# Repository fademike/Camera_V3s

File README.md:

# Camera_V3s
Webcam based on allwinner V3s and ESP8089

Simple 2 side board with Allwinner V3s, ov2640 and esp8089! 
(I didn't check the sound)

# How it works
Change wifi settings in file CONFIG_FILE <br>
Find ip in network by name. For example fing app: 
<br>
Watch the video on the MXPlayer(rtsp://192.168.10.22:8554/test), ffmpeg (ffplay -i rtsp://192.168.10.22:8554/test).. <br>
Watch the video on the Gstreamer: gst-launch-1.0 rtspsrc location="rtsp://192.168.10.22:8554/test" latency=0 ! rtph264depay ! decodebin ! videoconvert ! ximagesink <br>

# for QGroundControl:
TX: gst-launch-1.0 -v v4l2src device=/dev/video0 ! "video/x-raw,format=UYVY,width=800,height=600,framerate=10/1" ! videoconvert ! cedar_h264enc bitrate=2000 qp=15 keyint=10 ! rtph264pay pt=96 ! udpsink host=192.168.10.14 port=5600 <br>
RX on QGC or gstreamer: gst-launch-1.0 -v udpsrc port=5600 ! "application/x-rtp, media=(string)video, clock-rate=(int)90000, encoding-name=(string)H264, payload=(int)96" ! rtph264depay ! h264parse ! avdec_h264 ! videoconvert ! autovideosink <br>

v1.4 changed scheme and pcb. didn't check <br>
v1.2 in the previous commit. it works but there are errors errataSheet.txt in kicad

top             |  bottom
:-------------------------:|:-------------------------:
  |  

# How to build

git clone https://github.com/fademike/buildroot_v3s.git <br>
tar xf ~/Downloads/buildroot-2023.08.tar.xz <br>
cd buildroot-2023.08 <br>
ln -s ~/Downloads/buildroot/dl ./dl  # if you want <br>
make BR2_EXTERNAL=../buildroot_v3s licheepi_zero_defconfig (in dts you can change size of NOR flash) <br>
make <br>
make esp-rebuild && make <br>

# How to install

insert sd card.. <br>
./make_sd.sh <br>
run board camera_v3s from flash <br>
mount /dev/mmcblk0p1 /mnt <br>
flashcp /mnt/uboot_spi.bin /dev/mtd0 -v <br>
flashcp /mnt/zImage /dev/mtd1 -v <br>
flashcp /mnt/uboot_spi.bin /dev/mtd2 -v <br>
flashcp /mnt/rootfs.squashfs /dev/mtd3 -v <br>
flash_erase /dev/mtd4 0 1000.. <br>
add to mtd4 CONFIG_FILE to wifi settings, and init/deinit script of system <br>
init.sh script for example: <br>
test-launch  --gst-debug=3 '( v4l2src device=/dev/video0 ! video/x-raw,format=UYVY,width=800,height=600,framerate=10/1 ! videoconvert ! cedar_h264enc bitrate=2000 qp=15 keyint=10 ! rtph264pay name=pay0 pt=96 )' &

# note

The wi-fi is crashes after 30-50min. It was discussed on the forum (https://whycan.com/t_4326.html). I would like to change it to XR819, 88W8801 or others. 
You can connect usb wifi adapter (such as MT7601U) or solder a USB wifi module on bottom side.
I didn't notice any problems with the usb wifi adapter.

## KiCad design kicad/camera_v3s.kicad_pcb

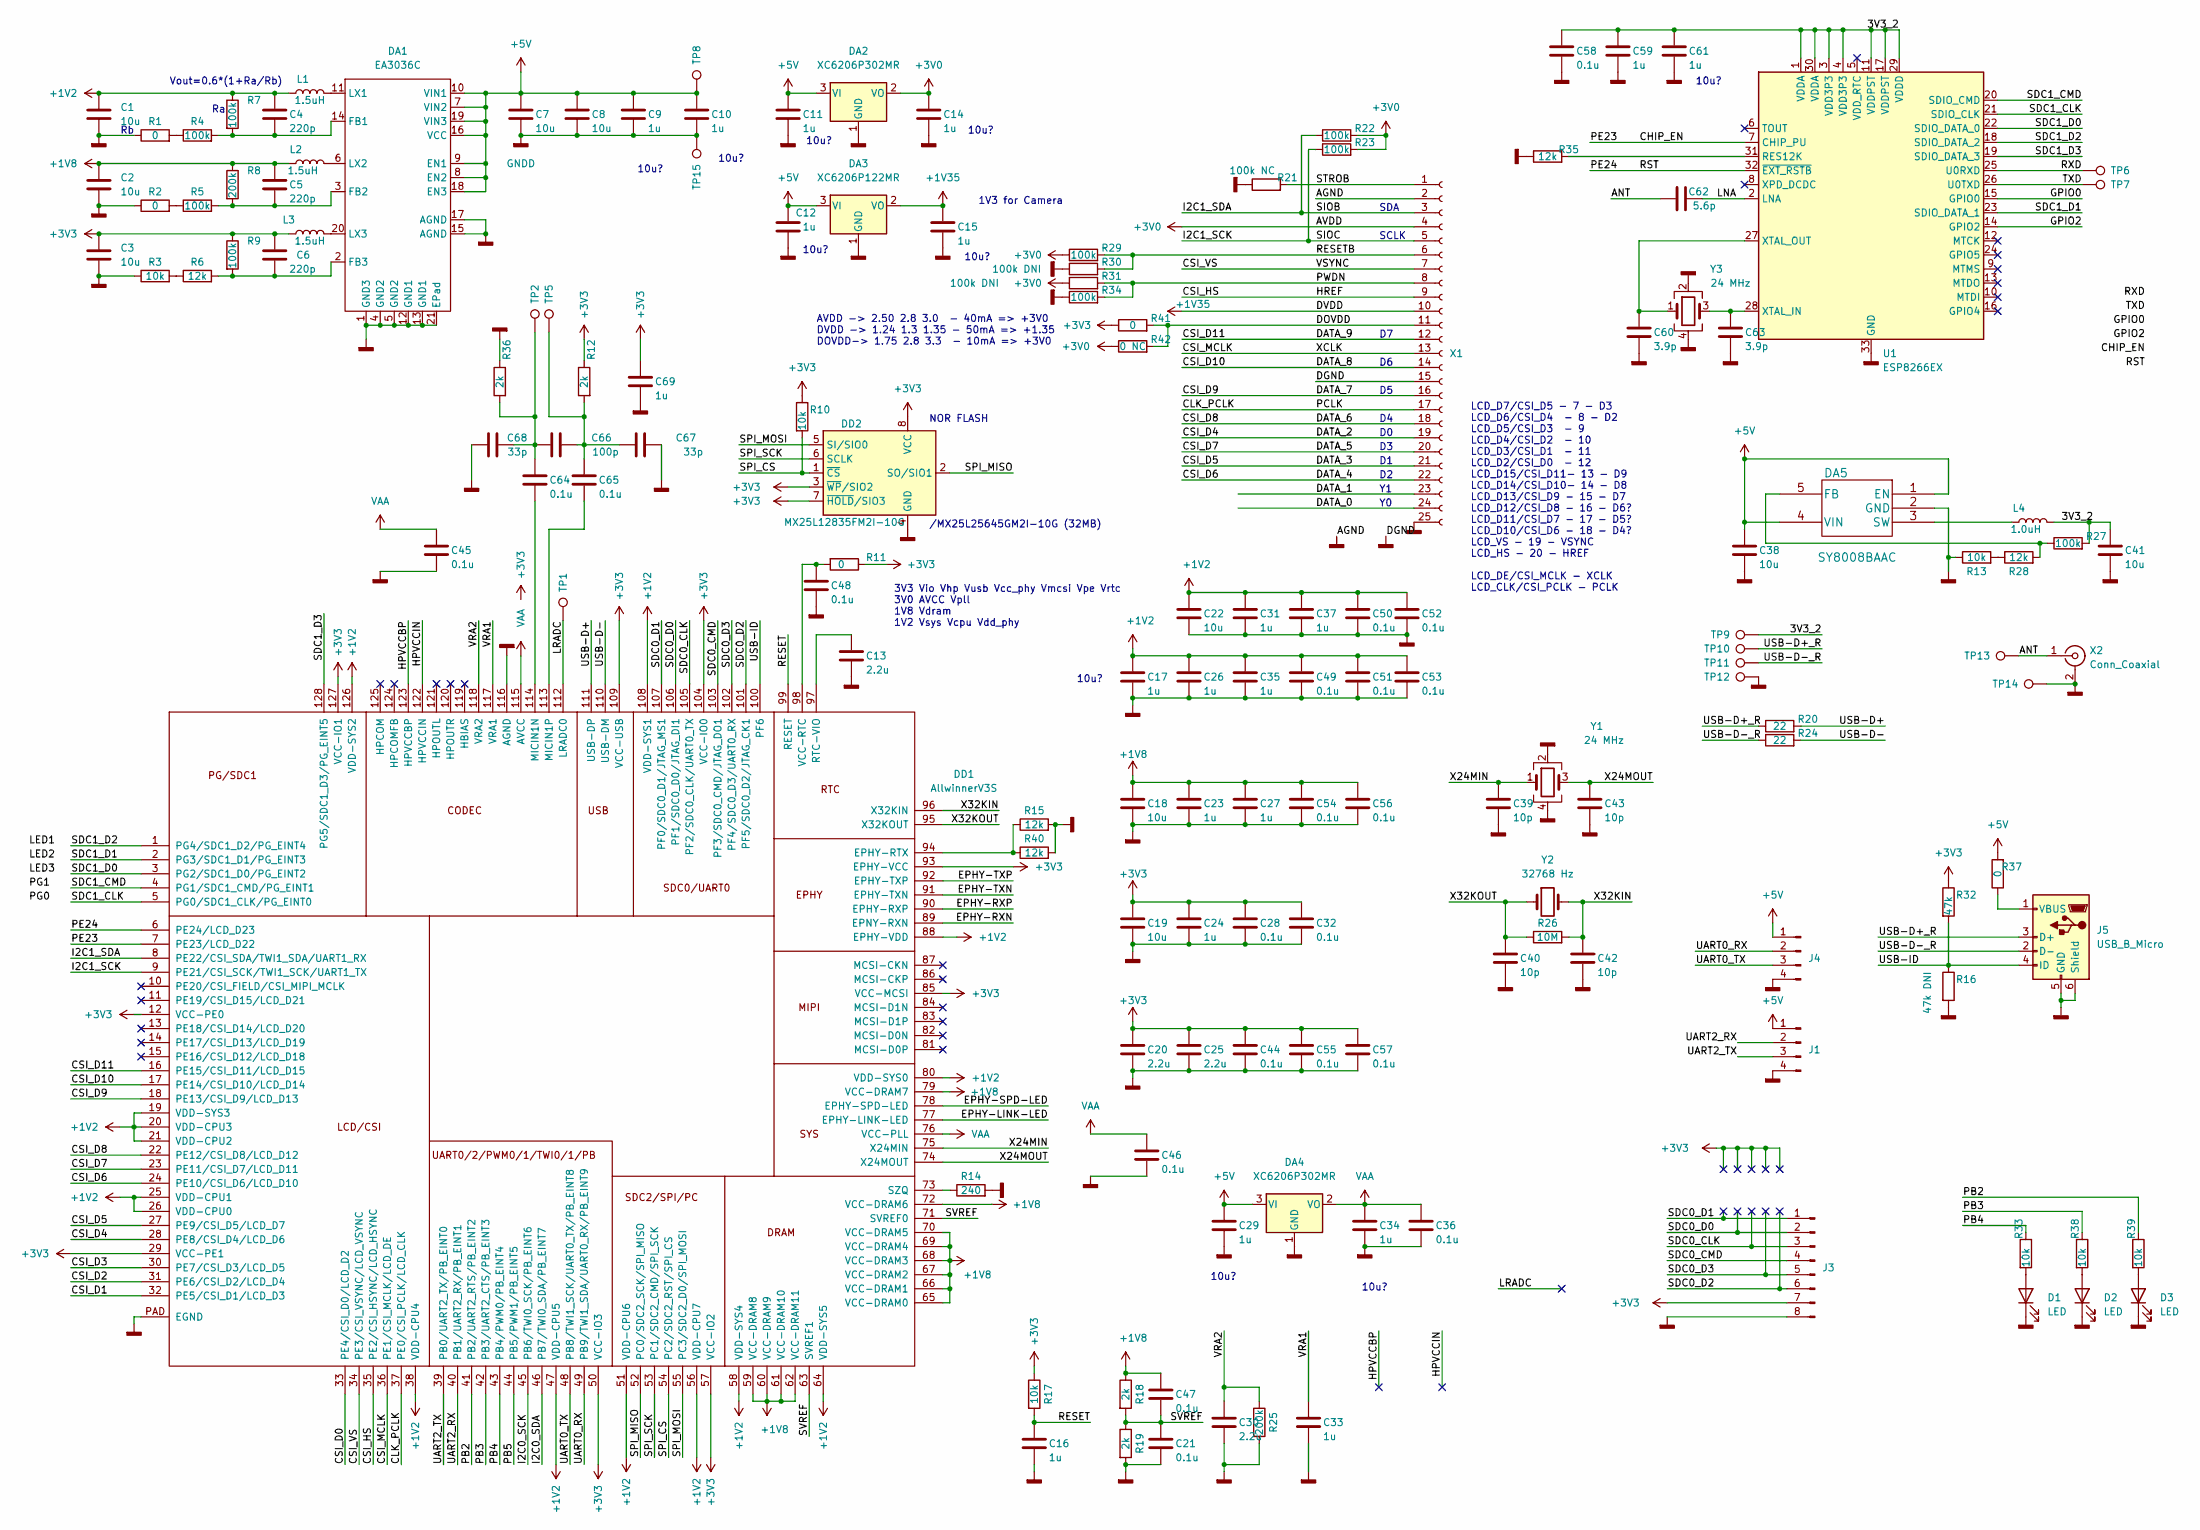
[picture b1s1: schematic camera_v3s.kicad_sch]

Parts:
C1, C2, C3, C7, C8, C18, C19, C22, C38, C41: 10u; C_0603_1608Metric; Voltage 6.3V
C4, C5, C6: 220p; C_0402_1005Metric; Voltage 6.3V
C9, C10, C11, C12, C14, C15, C16, C17, C23, C24, C26, C27, C29, C31, C33, C34, C35, C37, C59, C61, C69: 1u; C_0402_1005Metric; Voltage 6.3V
C13, C20, C25, C30: 2.2u; C_0402_1005Metric; Voltage 6.3V
C21, C28, C32, C36, C44, C45, C46, C47, C48, C49, C50, C51, C52, C53, C54, C55, C56, C57, C58, C64, C65: 0.1u; C_0402_1005Metric; Voltage 6.3V
C39, C40, C42, C43: 10p; C_0402_1005Metric; Voltage 6.3V
C60, C63: 3.9p; C_0402_1005Metric; Voltage 6.3V
C62: 5.6p; C_0402_1005Metric; Voltage 6.3V
C66: 100p; C_0402_1005Metric; Voltage 6.3V
C67, C68: 33p; C_0402_1005Metric; Voltage 6.3V
D1, D2, D3: LED; LED_0603_1608Metric
DA1: EA3036C; QFN-20-1EP_3x3mm_P0.4mm_EP1.65x1.65mm
DA2, DA4: XC6206P302MR; SOT-23
DA3: XC6206P122MR; SOT-23
DA5: SY8008BAAC; SOT-23-5
DD1: AllwinnerV3S; LQFP-128_14x14mm_P0.4mm
DD2: MX25L12835FM2I-10G; SOP-8_5.28x5.23mm_P1.27mm
J1, J4: Conn_01x04_Male; Molex_PicoBlade_53047-0410_1x04_P1.25mm_Vertical
J3: Conn_01x08_Male; Molex_PicoBlade_53047-0810_1x08_P1.25mm_Vertical
J5: USB_B_Micro; USB_Micro-B_Molex_47346-0001
L1, L2, L3: 1.5uH; L_1210_3225Metric
L4: 1.0uH; L_1210_3225Metric
R1, R2, R11, R41: 0; R_0402_1005Metric
R3, R10, R13, R17, R33, R38, R39: 10k; R_0402_1005Metric
R4, R5, R7, R9, R22, R23, R27, R29, R34: 100k; R_0402_1005Metric
R6, R15, R28, R35, R40: 12k; R_0402_1005Metric
R8, R25: 200k; R_0402_1005Metric
R12, R18, R19, R36: 2k; R_0402_1005Metric
R14: 240; R_0402_1005Metric
R16: 47k DNI; R_0402_1005Metric
R20, R24: 22; R_0402_1005Metric
R21: 100k NC; R_0402_1005Metric
R26: 10M; R_0402_1005Metric
R30, R31: 100k DNI; R_0402_1005Metric
R32: 47k; R_0402_1005Metric
R37: 0; R_0603_1608Metric
R42: 0 NC; R_0402_1005Metric
TP1, TP2, TP5, TP6, TP7, TP8, TP9, TP10, TP11, TP12, TP13, TP14, TP15: TestPoint; TestPoint_Pad_D1.0mm
U1: ESP8266EX; QFN-32-1EP_5x5mm_P0.5mm_EP3.45x3.45mm
X1: Conn_01x25_Female; CONN_FPC_24_0.5
X2: Conn_Coaxial; U.FL_Molex_MCRF_73412-0110_Vertical
Y1, Y3: 24 MHz; Crystal_SMD_3225-4Pin_3.2x2.5mm
Y2: 32768 Hz; Crystal_SMD_3215-2Pin_3.2x1.5mm

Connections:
+1V2: C1.1, C4.1, C17.1, C22.1, C26.1, C31.1, C35.1, C37.1, C49.1, C50.1, C51.1, C52.1, C53.1, DD1.19 (VDD-SYS3), DD1.20 (VDD-CPU3), DD1.21 (VDD-CPU2), DD1.25 (VDD-CPU1), DD1.26 (VDD-CPU0), DD1.38 (VDD-CPU4), DD1.47 (VDD-CPU5), DD1.51 (VDD-CPU6), DD1.56 (VDD-CPU7), DD1.58 (VDD-SYS4), DD1.64 (VDD-SYS5), DD1.80 (VDD-SYS0), DD1.88 (EPHY-VDD), DD1.108 (VDD-SYS1), DD1.126 (VDD-SYS2), L1.1, R7.1
+1V8: C2.1, C5.1, C18.1, C23.1, C27.1, C47.1, C54.1, C56.1, DD1.59 (VCC-DRAM8), DD1.60 (VCC-DRAM9), DD1.61 (VCC-DRAM10), DD1.62 (VCC-DRAM11), DD1.65 (VCC-DRAM0), DD1.66 (VCC-DRAM1), DD1.67 (VCC-DRAM2), DD1.68 (VCC-DRAM3), DD1.69 (VCC-DRAM4), DD1.70 (VCC-DRAM5), DD1.72 (VCC-DRAM6), DD1.79 (VCC-DRAM7), L2.1, R8.1, R18.1
+1V35: C15.1, DA3.2 (VO), X1.10
+3V0: C14.1, DA2.2 (VO), R22.2, R23.2, R29.1, R31.1, R42.1, X1.4
+3V3: C3.1, C6.1, C19.1, C20.1, C24.1, C25.1, C28.1, C32.1, C44.1, C55.1, C57.1, C69.1, DD1.12 (VCC-PE0), DD1.29 (VCC-PE1), DD1.50 (VCC-IO3), DD1.57 (VCC-IO2), DD1.85 (VCC-MCSI), DD1.93 (EPHY-VCC), DD1.104 (VCC-IO0), DD1.109 (VCC-USB), DD1.127 (VCC-IO1), DD2.3 (~WP/SIO2), DD2.7 (~HOLD/SIO3), DD2.8 (VCC), J3.7, L3.1, R9.1, R10.1, R11.1, R12.1, R17.1, R32.1, R41.1
+5V: C7.1, C8.1, C9.1, C10.1, C11.1, C12.1, C29.1, C38.1, DA1.7 (VIN2), DA1.8 (EN2), DA1.9 (EN1), DA1.10 (VIN1), DA1.16 (VCC), DA1.18 (EN3), DA1.19 (VIN3), DA2.3 (VI), DA3.3 (VI), DA4.3 (VI), DA5.1 (EN), DA5.4 (VIN), J1.1, J4.1, R37.2, TP8.1
/3V3_2: C41.1, C58.1, C59.1, C61.1, L4.2, R27.2, TP9.1, U1.1 (VDDA), U1.3 (VDD3P3), U1.4 (VDD3P3), U1.11 (VDDPST), U1.17 (VDDPST), U1.29 (VDDD), U1.30 (VDDA)
/ANT: C62.1, TP13.1, X2.1 (In)
/CHIP_EN: DD1.7 (PE23/LCD_D22), U1.7 (CHIP_PU)
/CLK_PCLK: DD1.37 (PE0/CSI_PCLK/LCD_CLK), X1.17
/CSI_D0: DD1.33 (PE4/CSI_D0/LCD_D2)
/CSI_D1: DD1.32 (PE5/CSI_D1/LCD_D3)
/CSI_D2: DD1.31 (PE6/CSI_D2/LCD_D4)
/CSI_D3: DD1.30 (PE7/CSI_D3/LCD_D5)
/CSI_D4: DD1.28 (PE8/CSI_D4/LCD_D6), X1.19
/CSI_D5: DD1.27 (PE9/CSI_D5/LCD_D7), X1.21
/CSI_D6: DD1.24 (PE10/CSI_D6/LCD_D10), X1.22
/CSI_D7: DD1.23 (PE11/CSI_D7/LCD_D11), X1.20
/CSI_D8: DD1.22 (PE12/CSI_D8/LCD_D12), X1.18
/CSI_D9: DD1.18 (PE13/CSI_D9/LCD_D13), X1.16
/CSI_D10: DD1.17 (PE14/CSI_D10/LCD_D14), X1.14
/CSI_D11: DD1.16 (PE15/CSI_D11/LCD_D15), X1.12
/CSI_HS: DD1.35 (PE2/CSI_HSYNC/LCD_HSYNC), X1.9
/CSI_MCLK: DD1.36 (PE1/CSI_MCLK/LCD_DE), X1.13
/CSI_VS: DD1.34 (PE3/CSI_VSYNC/LCD_VSYNC), X1.7
/DATA_0: X1.24
/DATA_1: X1.23
/DOVDD: R41.2, R42.2, X1.11
/EPHY-LINK-LED: DD1.77 (EPHY-LINK-LED)
/EPHY-RXN: DD1.89 (EPNY-RXN)
/EPHY-RXP: DD1.90 (EPHY-RXP)
/EPHY-SPD-LED: DD1.78 (EPHY-SPD-LED)
/EPHY-TXN: DD1.91 (EPHY-TXN)
/EPHY-TXP: DD1.92 (EPHY-TXP)
/GPIO0: U1.15 (GPIO0)
/GPIO2: U1.14 (GPIO2)
/HPVCCBP: DD1.123 (HPVCCBP)
/HPVCCIN: DD1.122 (HPVCCIN)
/I2C0_SCK: DD1.45 (PB6/TWI0_SCK/PB_EINT6)
/I2C0_SDA: DD1.46 (PB7/TWI0_SDA/PB_EINT7)
/I2C1_SCK: DD1.9 (PE21/CSI_SCK/TWI1_SCK/UART1_TX), R23.1, X1.5
/I2C1_SDA: DD1.8 (PE22/CSI_SDA/TWI1_SDA/UART1_RX), R22.1, X1.3
/LNA: C62.2, U1.2 (LNA)
/LRADC: DD1.112 (LRADC0), TP1.1
/PB2: DD1.41 (PB2/UART2_RTS/PB_EINT2), R39.1
/PB3: DD1.42 (PB3/UART2_CTS/PB_EINT3), R38.1
/PB4: DD1.43 (PB4/PWM0/PB_EINT4), R33.1
/PB5: DD1.44 (PB5/PWM1/PB_EINT5)
/PE24: DD1.6 (PE24/LCD_D23), U1.32 (~EXT_RSTB)
/PWDN: R31.2, R34.2, X1.8
/RESET: C16.1, DD1.99 (RESET), R17.2
/RESETB: R29.2, R30.2, X1.6
/RXD: TP6.1, U1.25 (U0RXD)
/SDC0_CLK: DD1.105 (PF2/SDC0_CLK/UART0_TX), J3.3
/SDC0_CMD: DD1.103 (PF3/SDC0_CMD/JTAG_DO1), J3.4
/SDC0_D0: DD1.106 (PF1/SDC0_D0/JTAG_DI1), J3.2
/SDC0_D1: DD1.107 (PF0/SDC0_D1/JTAG_MS1), J3.1
/SDC0_D2: DD1.101 (PF5/SDC0_D2/JTAG_CK1), J3.6
/SDC0_D3: DD1.102 (PF4/SDC0_D3/UART0_RX), J3.5
/SDC1_CLK: DD1.5 (PG0/SDC1_CLK/PG_EINT0), U1.21 (SDIO_CLK)
/SDC1_CMD: DD1.4 (PG1/SDC1_CMD/PG_EINT1), U1.20 (SDIO_CMD)
/SDC1_D0: DD1.3 (PG2/SDC1_D0/PG_EINT2), U1.22 (SDIO_DATA_0)
/SDC1_D1: DD1.2 (PG3/SDC1_D1/PG_EINT3), U1.23 (SDIO_DATA_1)
/SDC1_D2: DD1.1 (PG4/SDC1_D2/PG_EINT4), U1.18 (SDIO_DATA_2)
/SDC1_D3: DD1.128 (PG5/SDC1_D3/PG_EINT5), U1.19 (SDIO_DATA_3)
/SPI_CS: DD1.54 (PC2/SDC2_RST/SPI_CS), DD2.1 (~CS), R10.2
/SPI_MISO: DD1.52 (PC0/SDC2_SCK/SPI_MISO), DD2.2 (SO/SIO1)
/SPI_MOSI: DD1.55 (PC3/SDC2_D0/SPI_MOSI), DD2.5 (SI/SIO0)
/SPI_SCK: DD1.53 (PC1/SDC2_CMD/SPI_SCK), DD2.6 (SCLK)
/STROB: R21.2, X1.1
/SVREF: C21.1, C47.2, DD1.63 (SVREF1), DD1.71 (SVREF0), R18.2, R19.1
/TXD: TP7.1, U1.26 (U0TXD)
/UART0_RX: DD1.49 (PB9/TWI1_SDA/UART0_RX/PB_EINT9), J4.2
/UART0_TX: DD1.48 (PB8/TWI1_SCK/UART0_TX/PB_EINT8), J4.3
/UART2_RX: DD1.40 (PB1/UART2_RX/PB_EINT1), J1.2
/UART2_TX: DD1.39 (PB0/UART2_TX/PB_EINT0), J1.3
/USB-D+: DD1.111 (USB-DP), R20.2
/USB-D+_R: J5.3 (D+), R20.1, TP10.1
/USB-D-: DD1.110 (USB-DM), R24.2
/USB-D-_R: J5.2 (D-), R24.1, TP11.1
/USB-ID: DD1.100 (PF6), J5.4 (ID), R16.1, R32.2
/VRA1: C33.1, DD1.117 (VRA1)
/VRA2: C30.1, DD1.118 (VRA2), R25.1
/X24MIN: C39.1, DD1.75 (X24MIN), Y1.1
/X24MOUT: C43.1, DD1.74 (X24MOUT), Y1.3
/X32KIN: C42.1, DD1.96 (X32KIN), R26.2, Y2.2
/X32KOUT: C40.1, DD1.95 (X32KOUT), R26.1, Y2.1
GNDD: C1.2, C2.2, C3.2, C7.2, C8.2, C9.2, C10.2, C11.2, C12.2, C13.2, C14.2, C15.2, C16.2, C17.2, C18.2, C19.2, C20.2, C21.2, C22.2, C23.2, C24.2, C25.2, C26.2, C27.2, C28.2, C29.2, C30.2, C31.2, C32.2, C33.2, C34.2, C35.2, C36.2, C37.2, C38.2, C39.2, C40.2, C41.2, C42.2, C43.2, C44.2, C45.2, C46.2, C48.2, C49.2, C50.2, C51.2, C52.2, C53.2, C54.2, C55.2, C56.2, C57.2, C58.2, C59.2, C60.2, C61.2, C63.2, C67.2, C68.1, C69.2, D1.1 (K), D2.1 (K), D3.1 (K), DA1.1 (GND3), DA1.4 (GND2), DA1.5 (GND2), DA1.12 (GND1), DA1.13 (GND1), DA1.15 (AGND), DA1.17 (AGND), DA1.21 (EPad), DA2.1 (GND), DA3.1 (GND), DA4.1 (GND), DA5.2 (GND), DD1.116 (AGND), DD1.PAD (EGND), DD2.4 (GND), J1.4, J3.8, J4.4, J5.5 (GND), J5.6 (Shield), R1.1, R2.1, R3.1, R13.1, R14.2, R15.2, R16.2, R19.2, R21.1, R25.2, R30.1, R34.1, R35.1, R36.1, R40.2, TP12.1, TP14.1, TP15.1, U1.33 (GND), X1.2, X1.15, X1.25, X2.2 (Ext), Y1.2, Y1.4, Y3.2, Y3.4
unnamed: C64.1, C66.1, C68.2, R36.2, TP2.1
unnamed: C65.1, C66.2, C67.1, R12.2, TP5.1
unnamed: D1.2 (A), R33.2
unnamed: D2.2 (A), R38.2
unnamed: D3.2 (A), R39.2
unnamed: C4.2, DA1.14 (FB1), R4.2, R7.2
unnamed: C5.2, DA1.3 (FB2), R5.2, R8.2
unnamed: C6.2, DA1.2 (FB3), R6.2, R9.2
unnamed: DA1.11 (LX1), L1.2
unnamed: DA1.6 (LX2), L2.2
unnamed: DA1.20 (LX3), L3.2
unnamed: DA5.5 (FB), R27.1, R28.2
unnamed: DA5.3 (SW), L4.1
unnamed: DD1.94 (EPHY-RTX), R15.1, R40.1
unnamed: C64.2, DD1.114 (MICIN1N)
unnamed: C65.2, DD1.113 (MICIN1P)
unnamed: C13.1, DD1.97 (RTC-VIO)
unnamed: DD1.73 (SZQ), R14.1
unnamed: C48.1, DD1.98 (VCC-RTC), R11.2
unnamed: J5.1 (VBUS), R37.1
unnamed: R1.2, R4.1
unnamed: R2.2, R5.1
unnamed: R3.2, R6.1
unnamed: R13.2, R28.1
unnamed: R35.2, U1.31 (RES12K)
unnamed: C63.1, U1.28 (XTAL_IN), Y3.3
unnamed: C60.1, U1.27 (XTAL_OUT), Y3.1
VAA: C34.1, C36.1, C45.1, C46.1, DA4.2 (VO), DD1.76 (VCC-PLL), DD1.115 (AVCC)

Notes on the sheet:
10u?
3V3 Vio Vhp Vusb Vcc_phy Vmcsi Vpe Vrtc 3V0 AVCC Vpll 1V8 Vdram 1V2 Vsys Vcpu Vdd_phy
SCLK
1V3 for Camera
AVDD -> 2.50 2.8 3.0 - 40mA => +3V0 DVDD -> 1.24 1.3 1.35 - 50mA => +1.35 DOVDD-> 1.75 2.8 3.3 - 10mA => +3V0
NOR FLASH
LCD_D7/CSI_D5 - 7 - D3 LCD_D6/CSI_D4 - 8 - D2 LCD_D5/CSI_D3 - 9 LCD_D4/CSI_D2 - 10 LCD_D3/CSI_D1 - 11 LCD_D2/CSI_D0 - 12 LCD_D15/CSI_D11- 13 - D9 LCD_D14/CSI_D10- 14 - D8 LCD_D13/CSI_D9 - 15 - D7 LCD_D12/CSI_D8 - 16 - D6? LCD_D11/CSI_D7 - 17 - D5? LCD_D10/CSI_D6 - 18 - D4? LCD_VS - 19 - VSYNC LCD_H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
Vout=0.6*(1+Ra/Rb)
SDA
/MX25L25645GM2I-10G (32MB)

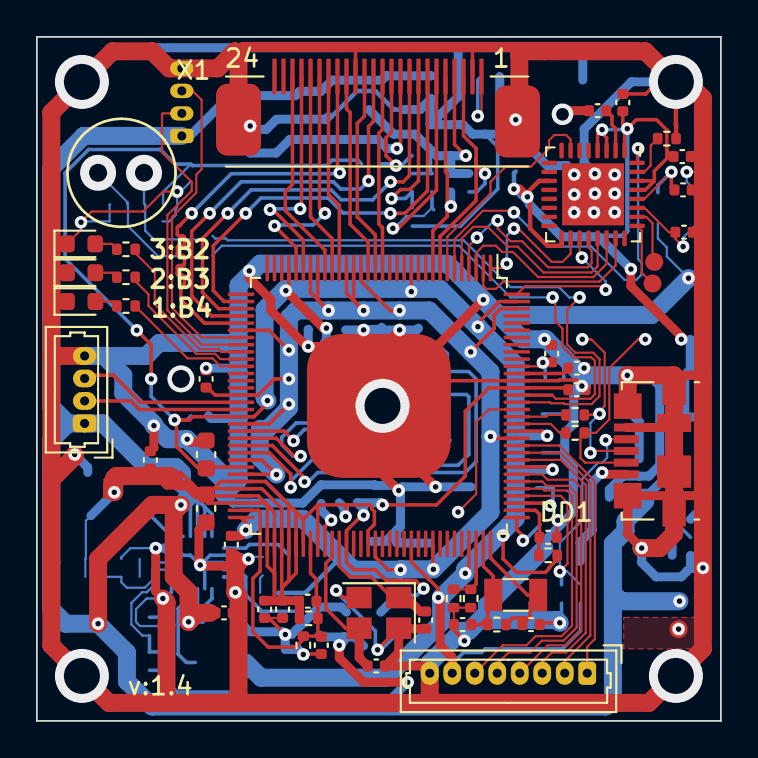
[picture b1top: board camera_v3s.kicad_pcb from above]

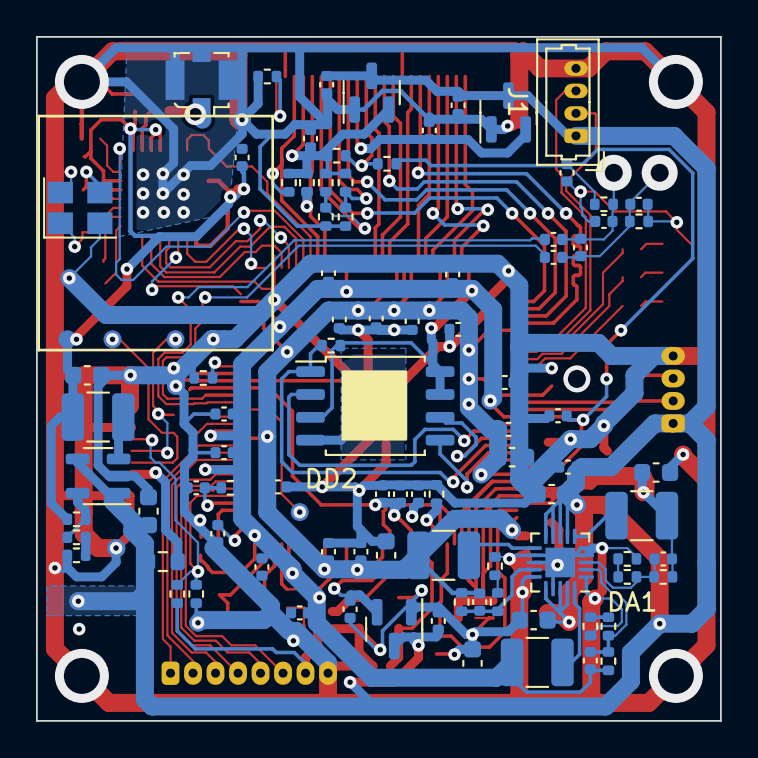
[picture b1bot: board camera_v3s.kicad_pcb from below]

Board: 2 copper layers, 38.0 x 38.0 mm, 148 parts (97 on the bottom side), 97 nets.

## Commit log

2023-12-03 v1.2 uploaded
2023-12-03 v1.4 changed scheme and pcb. did not tested version
2024-06-30 gstreamer cedar, rtsp-server added
2024-08-24 notes on wifi
